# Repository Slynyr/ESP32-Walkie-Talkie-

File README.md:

# ESP32 Walkie-Talkie
All firmware, documentation, and resources are available in the following repository. The ESP32 Walkie-Talkies make use of UDP over wifi in order to transmit audio. They function and operate just like every other Walkie-Talkie but with the benefits of a digital connection rather than an analog one.

## Features
* Oled display
* 12 bit speaker
* Built in battery with charge circuit
* Custom PCB design
* Custom 3d printed housing

## How it Works
The Walkie-Talkie makes use of a wifi enabled chip, the **WROOM-32**, in order to do digital communication via **UDP**. The ESP32 devboard has been modified to house a significantly larger antenna in order to increase the range to a tested 300+ meters. 

## Setup
### Arduino IDE
In order to upload the firmware to the ESP32 Walkie-Talkie, you will need to have the Arduino IDE setup for development on Espressif modules/chips. If you already have the appropriate environemnt setup, skip this step

> Downlaod the [Arduino IDE](https://www.arduino.cc/en/software) for your respective operating system

> Open the Arduino IDE and navigate to **Arduini IDE > Preferences**. Place the following url inside the **Additional board managers URL** box.  
`https://raw.githubusercontent.com/espressif/arduino-esp32/gh-pages/package_esp32_index.json`.

>Navigate to **Tool > Manage Libraries** and install the ***.

### Deploying
> Plug in your ESP32 Devboard and navigate to the **Board Manager** in the top left of your IDE. Select the appropriate board type and port for your respective devboard. If you are using a **WROOM32** based devboard as specified in the **BOM**, use the **WROOM-DA** board manager.
`Note: On some devboards, it may be necesary to hold down the boot button while uploading`

**Clearing Memory**
>Navigate to the **Tools > FlushEEPROM** and open the **FlushEEPROM.ino** file inside the Arduino IDE. We wrote this tool in order to allow us to flush the ESP32's memory. It also validates that all the bytes have been reset. Alternatively, you can use a web version, however, it does do any form of validation.
`https://adafruit.github.io/Adafruit_WebSerial_ESPTool/`

**Flashing Walkie-Talkie firmware**
> Navigate to the main folder and open **Main.Ino** file inside of the Arduino IDE.

## KiCad
The kicad folder contains all the project files, libraries and tools we created throughout the process. The following files can be accessed/opened via KiCad 6.

>Note: In order to properly load the project files in KiCad, you may be required to manually add both the footprint and symbol libraries manualy via the libraries manager in KiCad.

### KiCad Package Manager
Using github for version control can be a little finicky in the case of KiCad. When moving between machines, any non project specific libraries must be manually copied to the repo and then re-copied back in whenever a user pulls. In order to increase iteration time and make the whole process easier, A **CLI** tool was created to handle the copying process

> **SETUP**: When you first load the tool, you will be prompted for a initial setup, simply follow the instructions and input the file paths for both copy paths for KiCad and the Repository. Multiple copy paths can be added by using the "," seperator.

> **Commands:** Libraries can be copied between the source and destination paths by using ***push*** and ***pull*** respectively. The tool can also be reconfigured by running ***config***

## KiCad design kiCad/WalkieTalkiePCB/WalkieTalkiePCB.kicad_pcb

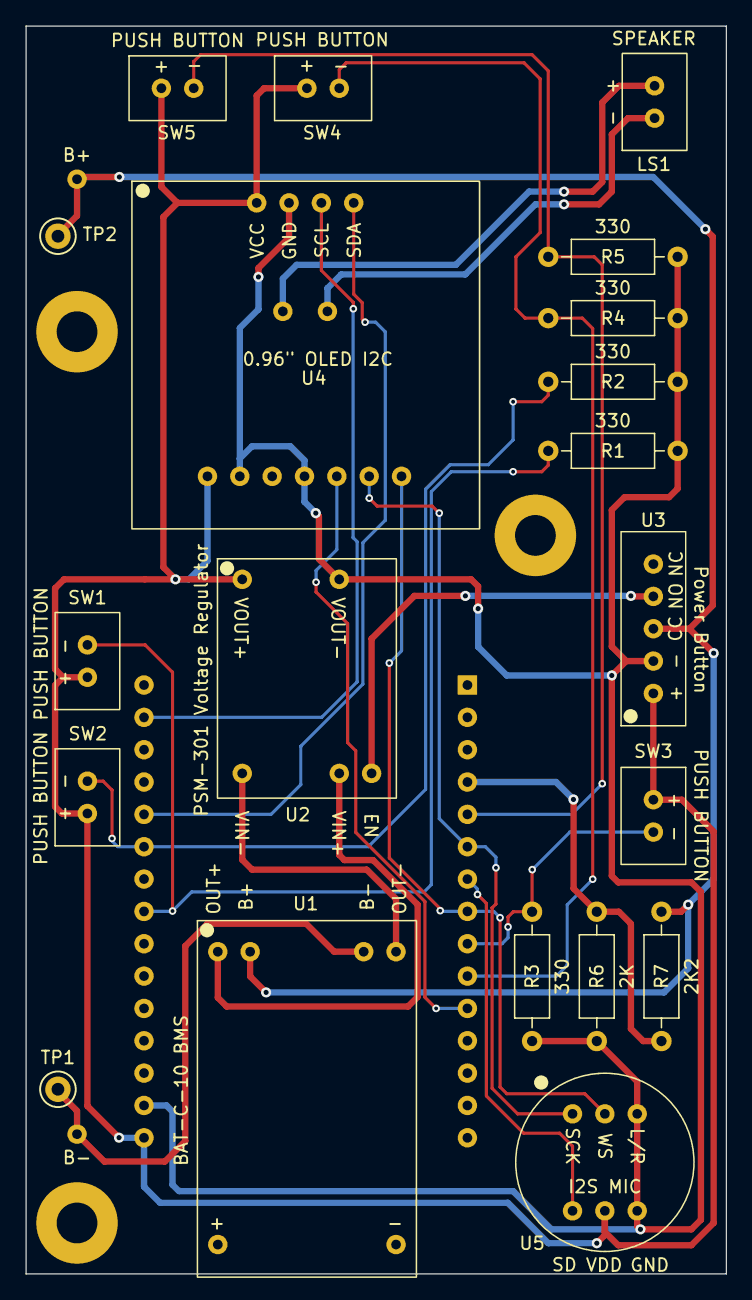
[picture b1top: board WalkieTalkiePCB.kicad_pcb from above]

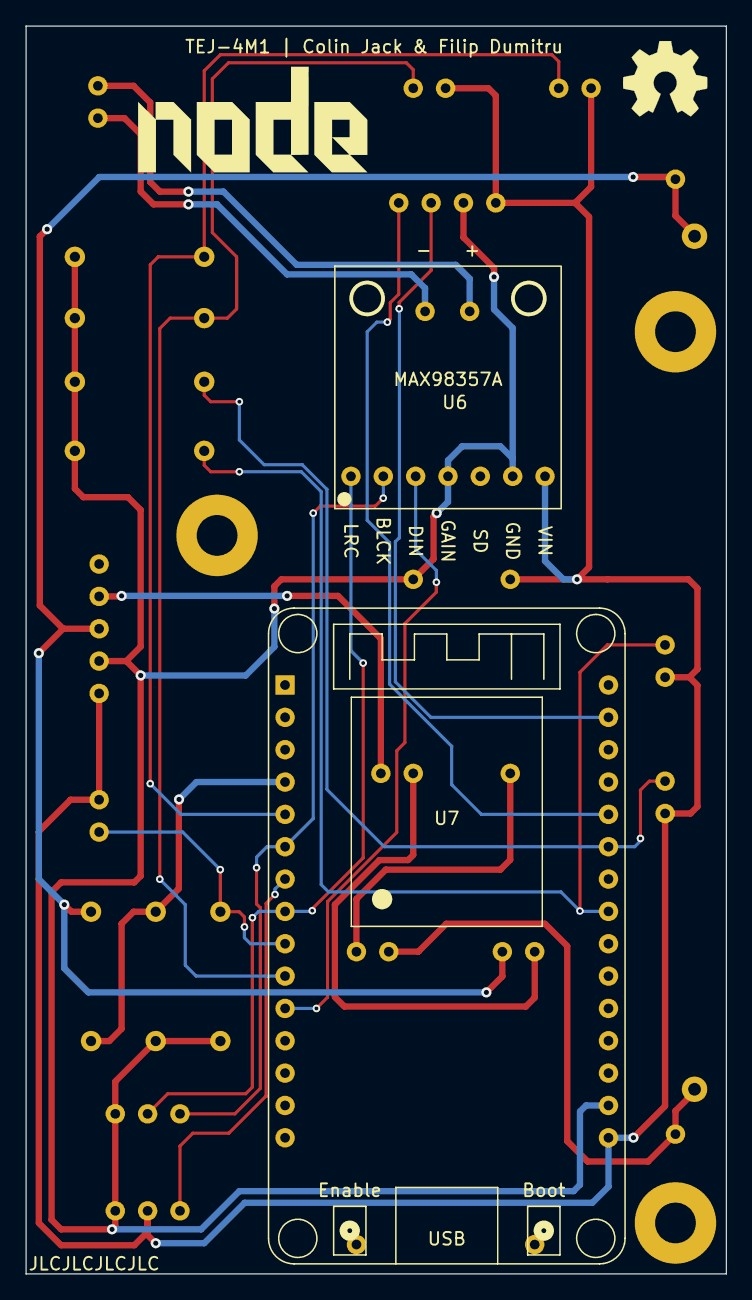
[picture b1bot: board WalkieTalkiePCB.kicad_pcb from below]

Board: 2 copper layers, 55.0 x 98.0 mm, 23 parts (2 on the bottom side), 21 nets.

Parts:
BT1: 18650 Lithium Cell; BATTERY-CONTACTS
LS1: Speaker; SPEAKER
R1, R2, R3, R4, R5: 330; R_Axial_DIN0207_L6.3mm_D2.5mm_P10.16mm_Horizontal
R6: 2K; R_Axial_DIN0207_L6.3mm_D2.5mm_P10.16mm_Horizontal
R7: 2K2; R_Axial_DIN0207_L6.3mm_D2.5mm_P10.16mm_Horizontal
SW1: UP; PUSH-BUTTON-CONTACTS
SW2: DWN; PUSH-BUTTON-CONTACTS
SW3: MODE; PUSH-BUTTON-CONTACTS
SW4: TLK; PUSH-BUTTON-CONTACTS
SW5: XTRA; PUSH-BUTTON-CONTACTS
TP1, TP2: TestPoint_Keystone_5000-5004_Miniature
U1: BAT-C-10TYPEC_(BMS); BAT-C-10TYPEC-BMS
U2: PSM-301-Voltage-Regulator-3.3V; PSM-301-Voltage-Regulator
U3: PBS-LED-1606WH-L_(Toggle_Button); PBS-LED-1606WH-L-Toggle-Switch
U4: I2C-128X64-OLED-LCD; I2S-128x64-OLED-LCD
U5: I2S-INMP441_(MIC); I2SINMP441-MIC
U6: MAX98357A; Amplifier
U7: ESP-WROOM-32; esp32_devkit_v1_doit

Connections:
GND: R1.1, R2.1, R3.1, R4.1, R5.1, R6.1, U2.2 (VOUT-), U3.2 (-), U4.2 (GND), U5.3 (L/R), U5.6 (GND), U6.4 (GAIN), U6.6 (GND), U7.29 (GND)
unnamed: BT1.1 (+), R7.2, TP2.1, U1.2 (B+), U3.3 (CC)
unnamed: BT1.2 (-), TP1.1, U1.3 (B-)
unnamed: R1.2, SW1.2, U7.23 (D5)
unnamed: R2.2, SW2.2, U7.21 (D19)
unnamed: R3.2, SW3.2, U7.9 (D26)
unnamed: R4.2, SW4.2, U7.10 (D27)
unnamed: R5.2, SW5.2, U7.5 (D35)
unnamed: R6.2, R7.1, U7.4 (D34)
unnamed: U1.1 (OUT+), U2.4 (VIN+)
unnamed: U1.4 (OUT-), U2.3 (VIN-)
unnamed: U2.5 (EN), U3.4 (NO)
unnamed: U4.3 (SCL), U7.17 (D22)
unnamed: U4.4 (SDA), U7.20 (D21)
unnamed: U5.1 (SCK), U6.2 (BLCK), U7.6 (D32)
unnamed: U5.2 (WS), U6.1 (LRC), U7.8 (D25)
unnamed: U5.4 (SD), U7.7 (D33)
unnamed: U6.3 (DIN), U7.11 (D14)
unnamed: LS1.1, U6.8 (-)
unnamed: LS1.2, U6.9 (+)
VCC: SW1.1, SW2.1, SW3.1, SW4.1, SW5.1, U2.1 (VOUT+), U3.1 (+), U4.1 (VCC), U5.5 (VDD), U6.7 (VIN), U7.30 (3V3)

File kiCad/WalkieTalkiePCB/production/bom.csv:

Designator,Footprint,Quantity,Value,LCSC Part #
BT1,BATTERY-CONTACTS,1,18650 Lithium Cell,
LS1,SPEAKER,1,Speaker,
"R1, R2, R3, R4, R5",R_Axial_DIN0207_L6.3mm_D2.5mm_P10.16mm_Horizontal,5,330,
R6,R_Axial_DIN0207_L6.3mm_D2.5mm_P10.16mm_Horizontal,1,2K,
R7,R_Axial_DIN0207_L6.3mm_D2.5mm_P10.16mm_Horizontal,1,2K2,
SW1,PUSH-BUTTON-CONTACTS,1,UP,
SW2,PUSH-BUTTON-CONTACTS,1,DWN,
SW3,PUSH-BUTTON-CONTACTS,1,MODE,
SW4,PUSH-BUTTON-CONTACTS,1,TLK,
SW5,PUSH-BUTTON-CONTACTS,1,XTRA,
U1,BAT-C-10TYPEC-BMS,1,BAT-C-10TYPEC_(BMS),
U2,PSM-301-Voltage-Regulator,1,PSM-301-Voltage-Regulator-3.3V,
U3,PBS-LED-1606WH-L-Toggle-Switch,1,PBS-LED-1606WH-L_(Toggle_Button),
U4,I2S-128x64-OLED-LCD,1,I2C-128X64-OLED-LCD,
U5,I2SINMP441-MIC,1,I2S-INMP441_(MIC),
U6,Amplifier,1,MAX98357A,
U7,esp32_devkit_v1_doit,1,ESP-WROOM-32,

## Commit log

2022-10-07 Innit Commit
2022-10-07 Multiple Files
2022-10-07 Battery indicator
    -ESP can now calculate voltage level based on battery
    -Dynamic battery level indicator
2022-10-07 Added Text Function
    drawText function allows you to quickly and easily draw text
2022-10-07 Node Connection Icons
    Added node connection Icons
2022-10-07 Add Voltage Readout
2022-10-07 Garbage Collecting
2022-10-07 Fixed drawText Function and added channel display
    - Fixed bug in drawText function where the cursor pos would not update
2022-10-07 UI and drawText function update
    - Added the ability to draw centered text
    - Added function to draw int with subheading (channel count/user count)
2022-10-08 Fixed usercount display
    Solved rendering issue caused by auto indentation with the user count graphic
2022-10-08 Added backdrop modes
    Added the ability to switch between UI backdrops
2022-10-09 Added centered circle function
    Added function that allows you to center both hollow and filled circles
2022-10-09 Start P2P Communication
    -Incomplete, and has not been included in the main file
2022-10-09 Improve voltage accuracy
    -Added state change function
    -Added low voltage popup
2022-10-11 Colin not workie
2022-10-12 Fixed state machine for battery Notification
    - Added battery low notification
    - Added debug button in order to dismiss notification
    - Added isActiveNotification bool which allows lower-screen elements to be easily hidden for other notifications in the future. This allows us to remain in the same state while still displaying notif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
2022-10-12 Button input system updated
    - Fixed button input system
    - NEW COMPILE ERROR in UpdateDisplay.h - To be resolved
2022-10-12 Change voltage math
    -More accurate voltage tracking
    -PB to dismiss works now
2022-10-12 Networking Demo
2022-10-14 Defining macAddress parsing
    - defined functions required to parse incoming mac-addresses and for keeping track of active mac-addresses
2022-10-15 WILL NOT COMPILE. Mac Address logic update
    Will need to rework some logic to support vectors since we are now passing strings
2022-10-15 Connections Counter Function
    Added the ability to count the nunber of active connections using the countConnections() function.
2022-10-17 Comment unfinished functions for compile
2022-10-18 Startup splashscreen
2022-10-18 Created sprites file
2022-10-20 MacAddress Management
    - Wrote functions for managing mac addresses in UDP mode
    (not functional)
2022-10-20 removed comment
2022-10-20 Debugging - Unverified
2022-10-20 Bugfixes and Refactoring
    - Created corresponding cpp files for each h file
    - Fixed MAC count compile errors
    - New bug where if they try to count a peered user, one will significantly slow down and loop
2022-10-21 Constructed mac vector strings, Optimization
2022-10-21 Debugging print statements & formatting
2022-10-23 Fix ESP crashing & bootloop
2022-10-24 Incomplete array mac addr manager
2022-10-24 Notes
2022-10-24 Rewrite using arduino arrays
    - Rename types to strings
2022-10-25 Array compile test
2022-10-25 Bootlooping
2022-10-25 Got User Count Working
    - Lowered loading screen time
    - Raised battery poll time
2022-10-26 Long press button interaction
    Added first test of long press and short press button interaction for up button (temporarily binded the same as debug button)
2022-10-27 Unsuccessful Debugging
2022-10-27 Debug Line
2022-10-31 Fixed finding empty array slot bug
2022-10-31 Debug Tests
    - Added dumpArray Function for printing all contents of a given array to serial.
2022-11-05 Removed unnecessary comments
2022-11-06 Fixed P2PConnect MacAddress logging
    - Fixed Mac Address logging for P2PConnect
    - User count now works
2022-11-06 Update TODO
2022-11-08 Update pushbutton function - Unverified - Won't work
    - Button status will clear due to being a local variable
    - Must keep a set of global variables for each button
2022-11-08 Create button structure
2022-11-08 Reformat buttons to be checked within the function
2022-11-09 Button Input System Debugging & Fixes
    - buttons structure and array declaration now in header file
2022-11-09 Incomplete millis based P2P implementation
    - Generated new folder for temp scripts
    - Included incomplete P2P millis script
2022-11-09 Testing buttons
2022-11-11 Fixed Button Function
    - Fixed Button Function
    - Added channel counter
2022-11-13 Fix short press unresponsive
2022-11-15 Unfunctional Settings Display
2022-11-16 Implemented RenderMenu
    - Implemented the bare bones of RenderMenu function, giving us the ability to render out a list of options and rendering different styles between selected and unselected items
2022-11-16 Implement Same Press Detection
2022-11-17 Updated Selected Styling
    Updated styling for selected render menu element
2022-11-17 Added decreasing channel count
2022-11-17 Update Menu Template
2022-11-18 Refactoring and Added Menu Label
2022-11-23 Updated position iterator to be universal
2022-11-24 Debugging Updates
2022-11-24 Debugging Update
2022-11-30 Created KiCad Project
2022-12-01 Battery Monitor Fix
2022-12-01 Microphone Test
    -Completed Multicore setup
    -Completed Microphone test with serial plotter
    -Mic might be DOA
2022-12-01 KiCad Schematic Update
2022-12-02 Bug fixes and visual changes to user prompts
2022-12-02 Visual Changes to promptBool
    - Finalized visual changes to prompt bool function
2022-12-06 Updated bool and int configurator
2022-12-07 Kicad
2022-12-08 Kicad Update
2022-12-15 Fix I2S Mic
    - IDF bug, where channels are swapped, change to right channel
2022-12-19 Kicad Footprints
2022-12-21 I2S Audio Passthrough Test
2022-12-21 test code - i2s
2022-12-23 Update Audio Process for Better Quality
2022-12-24 Updated PCB schematic
2022-12-24 Added symbols to git repo
2022-12-24 Kicad Finalized Schematic
    Colin Jack is smort
2022-12-24 Update Button Pins
2022-12-28 PCB
    Why do we live. Just to suffer.
2022-12-28 Added Libraries to repository
2022-12-29 Final Route of PCB
    - Generated JLC gerber
    - Created BOM
2022-12-29 Moved Silkscreen Elements
    Slikscreen
2022-12-29 Update Gerber
2022-12-29 Repo Formatting & Kicad update
2022-12-29 add SVG
2022-12-29 Updated Schematic Annotation
2022-12-30 Repo cleanup
2023-01-07 Debug
2023-01-07 Changes to Audio buffer and UDP broadcast
2023-01-07 Audio Receiving and Sending
    - Talk button states
    - Fixed debug passthrough state
    - Updated Todo
2023-01-07 Fix Watchdog Timer Trip
2023-01-07 Optimize Audio
    - Replace I2S start and stop with zeroing TX buffer
2023-01-08 Configurator Update
2023-01-08 Update Todo and write to EEPROM
2023-01-09 Updated Configurator and Update Display
    - Configurator now works and has integrated calculations for battery offset
    - Configurator now has an initializer in order to retrieve stored values on boot
    - pretified Options menu
    - created uiHeader() method
    - Updated old method that didnt use new input system
    - Created tool for flushing EEPROM memory
2023-01-10 Solved Merge Error
2023-01-11 Added read me
2023-01-26 Multiple improvements and fixes
2023-09-14 Updated README
    <README>
    - Removed wording and formatting errors from readme
